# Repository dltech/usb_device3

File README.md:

# usb_device3
USB HID gamepad.
STM32 based USB adapter for ZX spectrum joystick. You may connect gamepad
with d-pad and two buttons to PC using USB.
Tested and working.

Project structure:\
/result - here is all usefull files to try this project (firmware binary, schematic and pcb template)\
/lib - basic code directory\
/lib/regs - stm32 MCU registers (lowest micriocontroller API level)\
/lib/STM32F103_CMSIS/ - MCU specific part of CMSIS\
/lib/CMSIS_5 - ARM CMSIS abstraction level directly from arm, as a submodule\
fpjat - build and upload script (for xubuntu, needs gcc arm toolchain and st-link, see pdf)\
/doc - project documentation in tex\
/datasheet - all related documentation (datasheets, standards)\
/sch - KiCAD schematic project\
More information about device is in blog:\
https://dltecc.blogspot.com/2021/10/continue-on-your-own-risk-cmsis-v5.html \
https://dltecc.blogspot.com/2021/09/report-descriptor-example.html \
https://dltecc.blogspot.com/2021/11/usb-hid-driver-for-stm32.html

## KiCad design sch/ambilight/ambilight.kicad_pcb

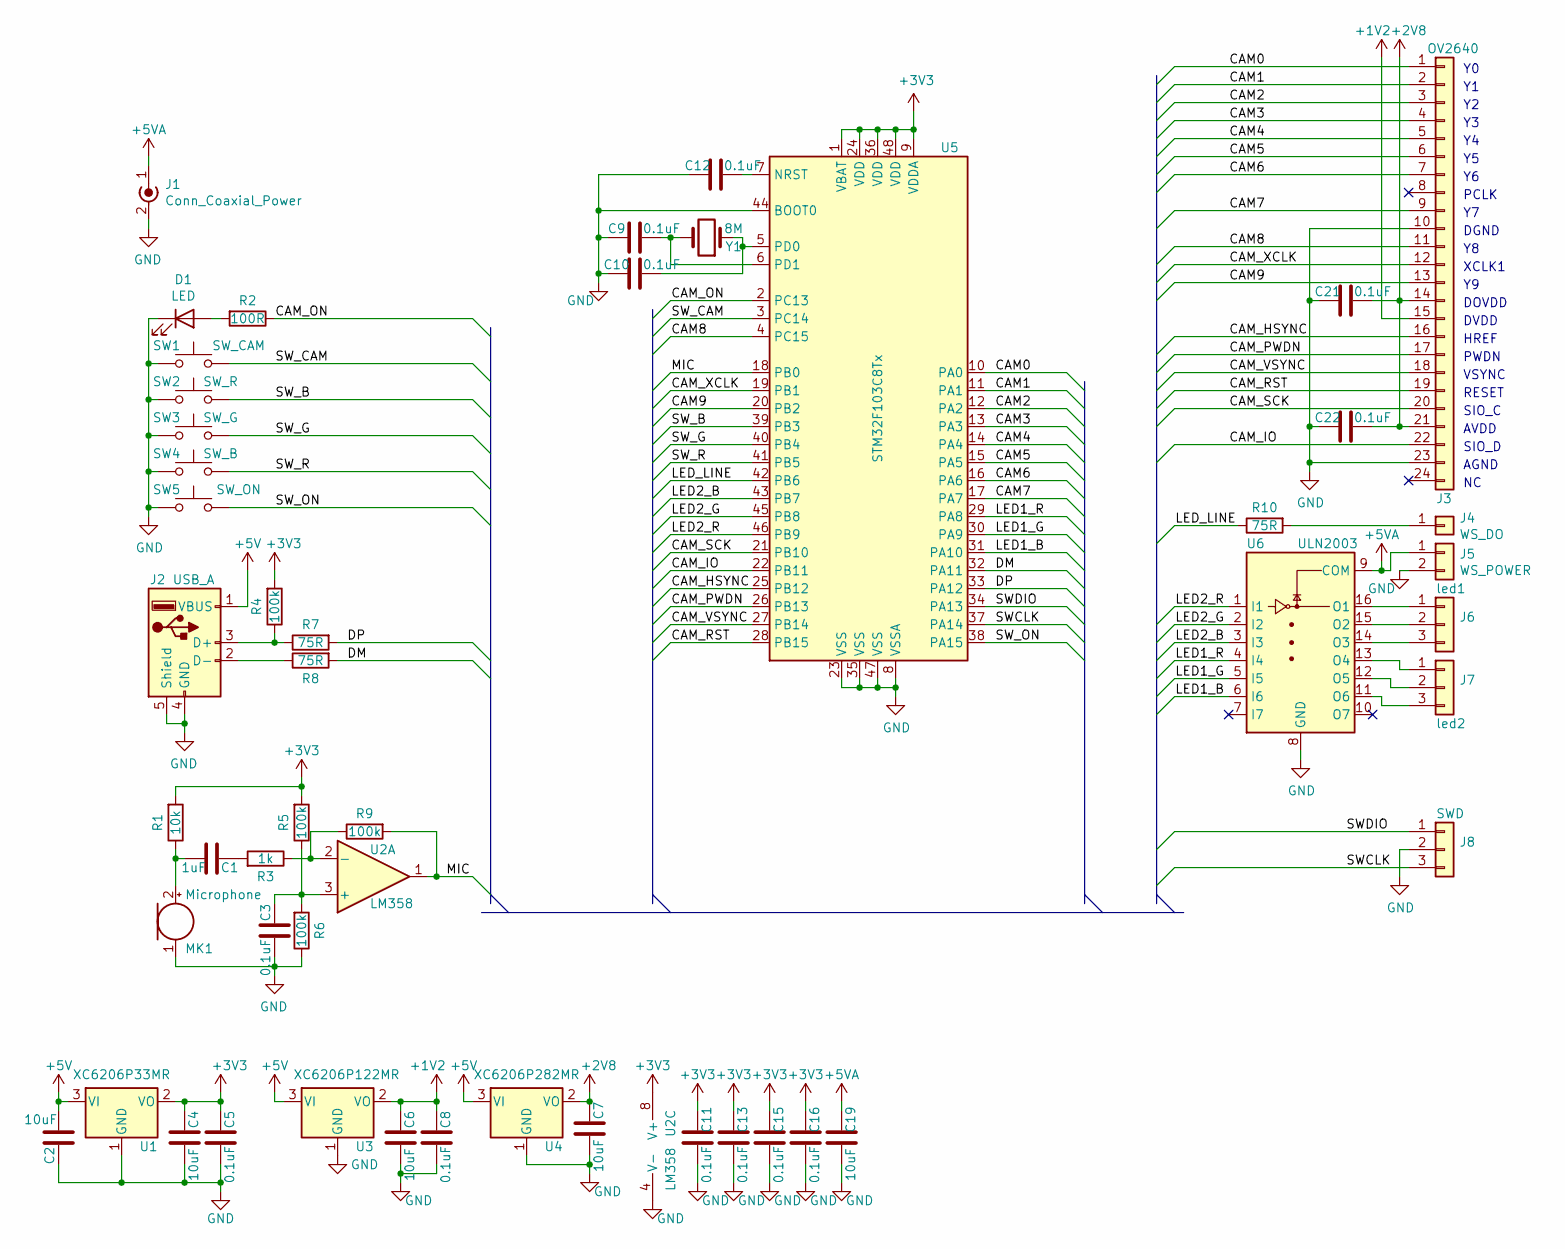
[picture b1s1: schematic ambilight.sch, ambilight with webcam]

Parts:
C1: 1uF; C_0805_2012Metric
C2, C4, C6, C7, C19: 10uF; C_0805_2012Metric
C3, C5, C8, C9, C10, C11, C12, C13, C15, C16, C21, C22: 0.1uF; C_0402_1005Metric
D1: LED; LED_0805_2012Metric
J1: Conn_Coaxial_Power; PinHeader_1x02_P2.54mm_Vertical
J2: USB_A; PinHeader_1x04_P2.54mm_Vertical
J3: OV2640; Hirose_FH12-24S-0.5SH_1x24-1MP_P0.50mm_Horizontal
J4: WS_DO; PinHeader_1x01_P2.54mm_Vertical
J5: WS_POWER; PinHeader_1x02_P2.54mm_Vertical
J6: led1; PinHeader_1x03_P2.54mm_Vertical
J7: led2; PinHeader_1x03_P2.54mm_Vertical
J8: SWD; 3WIRE_PADS
MK1: Microphone; CP_Radial_D5.0mm_P2.50mm
R1: 10k; R_0402_1005Metric
R2: 100R; R_0402_1005Metric
R3: 1k; R_0402_1005Metric
R4, R5, R6, R9: 100k; R_0402_1005Metric
R7, R8, R10: 75R; R_0402_1005Metric
SW1: SW_CAM; smd_sw_ali
SW2: SW_R; smd_sw_ali
SW3: SW_G; smd_sw_ali
SW4: SW_B; smd_sw_ali
SW5: SW_ON; smd_sw_ali
U1: XC6206P33MR; SOT-23
U2: LM358; SO-8_3.9x4.9mm_P1.27mm
U3: XC6206P122MR; SOT-23
U4: XC6206P282MR; SOT-23
U5: STM32F103C8Tx; LQFP-48_7x7mm_P0.5mm
U6: ULN2003; SOIC-16_3.9x9.9mm_P1.27mm
Y1: 8M; Crystal_SMD_5032-2Pin_5.0x3.2mm

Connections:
+1V2: C6.2, C8.2, J3.15, U3.2 (VO)
+2V8: C7.2, C21.1, C22.1, J3.14, J3.21, U4.2 (VO)
+3V3: C4.2, C5.2, C11.2, C13.2, C15.2, C16.2, R1.2, R4.2, R5.2, U1.2 (VO), U2.8 (V+), U5.1 (VBAT), U5.9 (VDDA), U5.24 (VDD), U5.36 (VDD), U5.48 (VDD)
+5V: C2.2, J2.1 (VBUS), U1.3 (VI), U3.3 (VI), U4.3 (VI)
+5VA: C19.2, J1.1 (In), J5.1, U6.9 (COM)
/CAM0: J3.1, U5.10 (PA0)
/CAM1: J3.2, U5.11 (PA1)
/CAM2: J3.3, U5.12 (PA2)
/CAM3: J3.4, U5.13 (PA3)
/CAM4: J3.5, U5.14 (PA4)
/CAM5: J3.6, U5.15 (PA5)
/CAM6: J3.7, U5.16 (PA6)
/CAM7: J3.9, U5.17 (PA7)
/CAM8: J3.11, U5.4 (PC15)
/CAM9: J3.13, U5.20 (PB2)
/CAM_HSYNC: J3.16, U5.25 (PB12)
/CAM_IO: J3.22, U5.22 (PB11)
/CAM_ON: R2.1, U5.2 (PC13)
/CAM_PWDN: J3.17, U5.26 (PB13)
/CAM_RST: J3.19, U5.28 (PB15)
/CAM_SCK: J3.20, U5.21 (PB10)
/CAM_VSYNC: J3.18, U5.27 (PB14)
/CAM_XCLK: J3.12, U5.19 (PB1)
/DM: R8.2, U5.32 (PA11)
/DP: R7.2, U5.33 (PA12)
/LED1_B: U5.31 (PA10), U6.6 (I6)
/LED1_G: U5.30 (PA9), U6.5 (I5)
/LED1_R: U5.29 (PA8), U6.4 (I4)
/LED2_B: U5.43 (PB7), U6.3 (I3)
/LED2_G: U5.45 (PB8), U6.2 (I2)
/LED2_R: U5.46 (PB9), U6.1 (I1)
/LED_LINE: R10.1, U5.42 (PB6)
/MIC: R9.2, U2.1, U5.18 (PB0)
/SWCLK: J8.3, U5.37 (PA14)
/SWDIO: J8.1, U5.34 (PA13)
/SW_B: SW2.2, U5.39 (PB3)
/SW_CAM: SW1.2, U5.3 (PC14)
/SW_G: SW3.2, U5.40 (PB4)
/SW_ON: SW5.2, U5.38 (PA15)
/SW_R: SW4.2, U5.41 (PB5)
GND: C2.1, C3.1, C4.1, C5.1, C6.1, C7.1, C8.1, C9.2, C10.2, C11.1, C12.2, C13.1, C15.1, C16.1, C19.1, C21.2, C22.2, D1.1 (K), J1.2 (Ext), J2.4 (GND), J2.5 (Shield), J3.10, J3.23, J5.2, J8.2, MK1.1 (-), R6.1, SW1.1, SW2.1, SW3.1, SW4.1, SW5.1, U1.1 (GND), U2.4 (V-), U3.1 (GND), U4.1 (GND), U5.8 (VSSA), U5.23 (VSS), U5.35 (VSS), U5.44 (BOOT0), U5.47 (VSS), U6.8 (GND)
unnamed: C1.1, R3.2
unnamed: C1.2, MK1.2 (+), R1.1
unnamed: C3.2, R5.1, R6.2, U2.3 (+)
unnamed: C9.1, U5.6 (PD1), Y1.2
unnamed: C10.1, U5.5 (PD0), Y1.1
unnamed: C12.1, U5.7 (NRST)
unnamed: D1.2 (A), R2.2
unnamed: J2.2 (D-), R8.1
unnamed: J2.3 (D+), R4.1, R7.1
unnamed: J4.1, R10.2
unnamed: J6.1, U6.16 (O1)
unnamed: J6.2, U6.15 (O2)
unnamed: J6.3, U6.14 (O3)
unnamed: J7.1, U6.13 (O4)
unnamed: J7.2, U6.12 (O5)
unnamed: J7.3, U6.11 (O6)
unnamed: R3.1, R9.1, U2.2 (-)

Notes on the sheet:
PCLK
DGND
XCLK1
DOVDD
DVDD
HREF
PWDN
VSYNC
RESET
SIO_C
AVDD
SIO_D
AGND

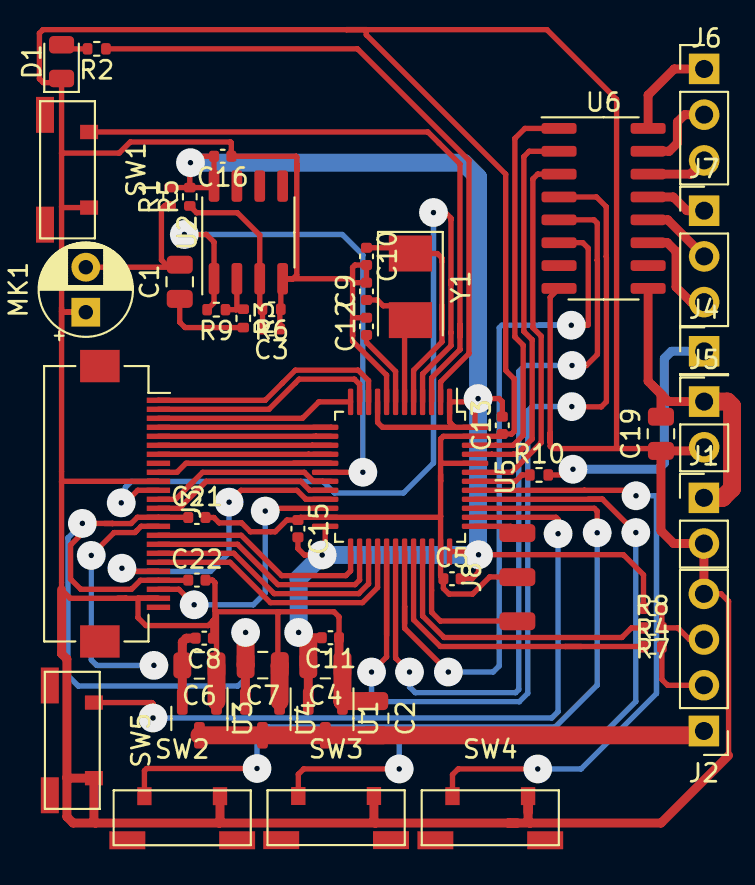
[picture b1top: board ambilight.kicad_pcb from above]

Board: 2 copper layers, 50 parts (0 on the bottom side), 58 nets.

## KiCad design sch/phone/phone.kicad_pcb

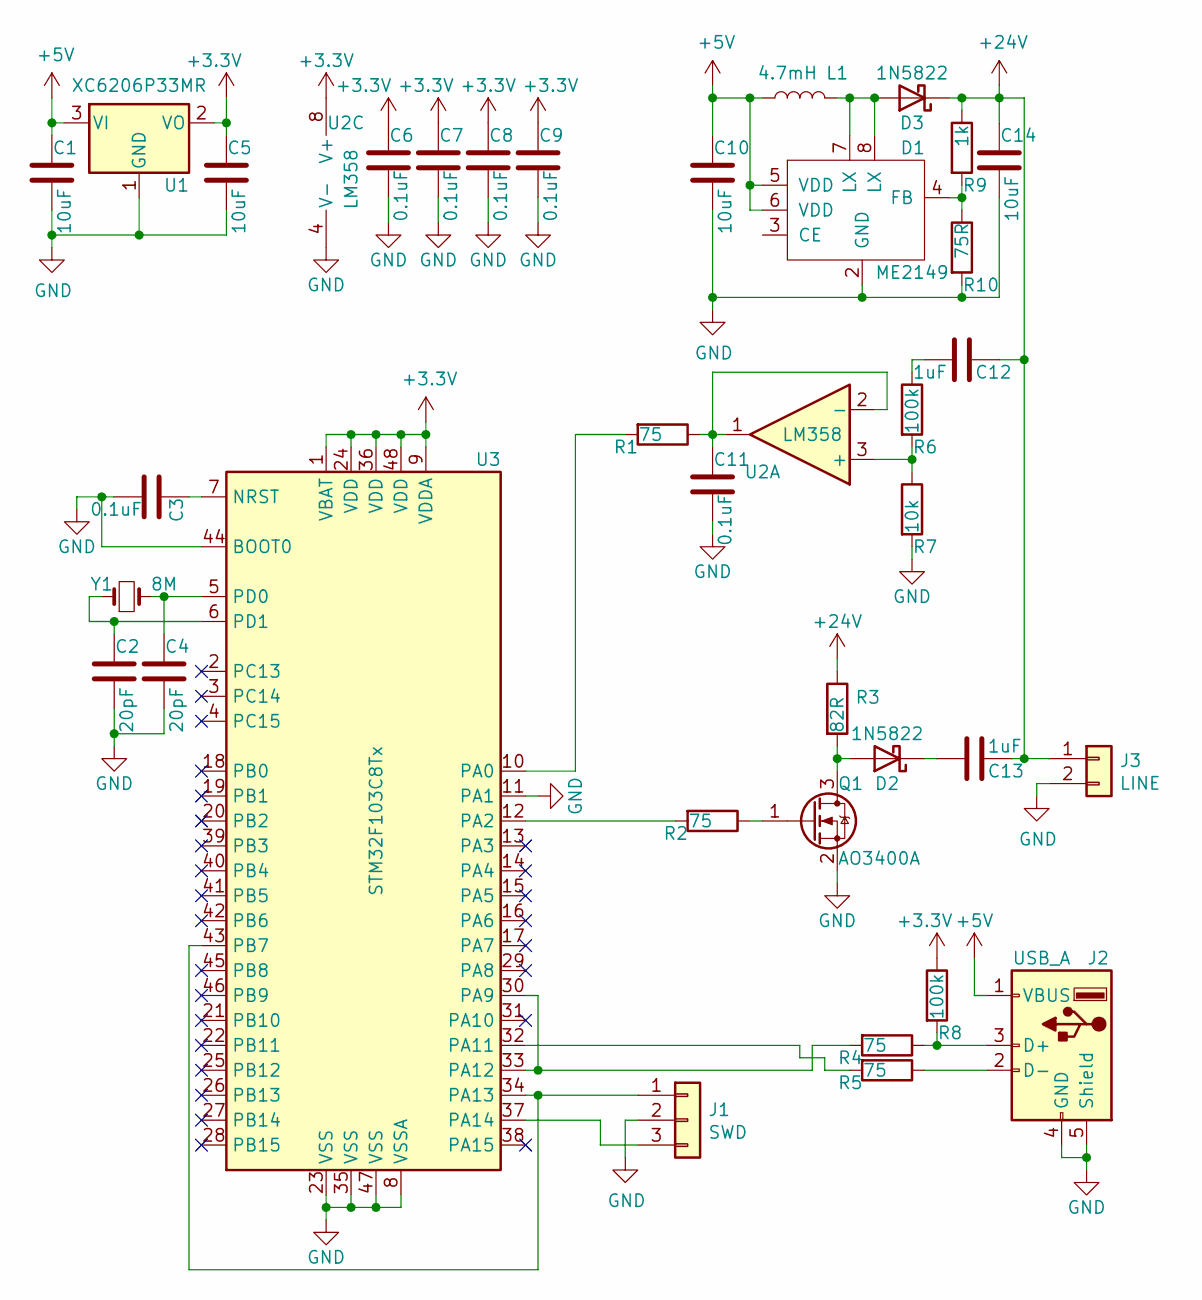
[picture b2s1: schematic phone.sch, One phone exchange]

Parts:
C1, C5, C10, C14: 10uF; C_0805_2012Metric
C2, C4: 20pF; C_0402_1005Metric
C3, C6, C7, C8, C9, C11: 0.1uF; C_0402_1005Metric
C12, C13: 1uF; C_0805_2012Metric
D1: ME2149; SO-8_3.9x4.9mm_P1.27mm
D2, D3: 1N5822; D_SMA
J1: SWD; 3WIRE_PADS
J2: USB_A; USB_A_CNCTech_1001-011-01101_Horizontal
J3: LINE; PinHeader_1x02_P1.27mm_Vertical
L1: 4.7mH; L_7.3x7.3_H3.5
Q1: AO3400A; SOT-23
R1, R2, R4, R5: 75; R_0402_1005Metric
R3: 82R; R_1206_3216Metric
R6, R8: 100k; R_0402_1005Metric
R7: 10k; R_0402_1005Metric
R9: 1k; R_0402_1005Metric
R10: 75R; R_0402_1005Metric
U1: XC6206P33MR; SOT-23
U2: LM358; SO-8_3.9x4.9mm_P1.27mm
U3: STM32F103C8Tx; LQFP-48_7x7mm_P0.5mm
Y1: 8M; Crystal_SMD_5032-2Pin_5.0x3.2mm

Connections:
+3V3: C5.1, C6.1, C7.1, C8.1, C9.1, R8.1, U1.2 (VO), U2.8 (V+), U3.1 (VBAT), U3.9 (VDDA), U3.24 (VDD), U3.36 (VDD), U3.48 (VDD)
+5V: C1.1, C10.1, D1.5 (VDD), D1.6 (VDD), J2.1 (VBUS), L1.1, U1.3 (VI)
+24V: C12.1, C13.1, C14.1, D3.1 (K), J3.1, R3.1, R9.1
GND: C1.2, C2.2, C3.2, C4.2, C5.2, C6.2, C7.2, C8.2, C9.2, C10.2, C11.2, C14.2, D1.2 (GND), J1.2, J2.4 (GND), J2.5 (Shield), J3.2, Q1.2 (S), R7.2, R10.2, U1.1 (GND), U2.4 (V-), U3.8 (VSSA), U3.11 (PA1), U3.23 (VSS), U3.35 (VSS), U3.44 (BOOT0), U3.47 (VSS)
unnamed: C2.1, U3.6 (PD1), Y1.1
unnamed: C3.1, U3.7 (NRST)
unnamed: C4.1, U3.5 (PD0), Y1.2
unnamed: C11.1, R1.1, U2.1, U2.2 (-)
unnamed: C12.2, R6.1
unnamed: C13.2, D2.1 (K)
unnamed: D1.4 (FB), R9.2, R10.1
unnamed: D1.7 (LX), D1.8 (LX), D3.2 (A), L1.2
unnamed: D2.2 (A), Q1.3 (D), R3.2
unnamed: J1.1, U3.34 (PA13), U3.43 (PB7)
unnamed: J1.3, U3.37 (PA14)
unnamed: J2.2 (D-), R5.1
unnamed: J2.3 (D+), R4.1, R8.2
unnamed: Q1.1 (G), R2.1
unnamed: R1.2, U3.10 (PA0)
unnamed: R2.2, U3.12 (PA2)
unnamed: R4.2, U3.30 (PA9), U3.33 (PA12)
unnamed: R5.2, U3.32 (PA11)
unnamed: R6.2, R7.1, U2.3 (+)

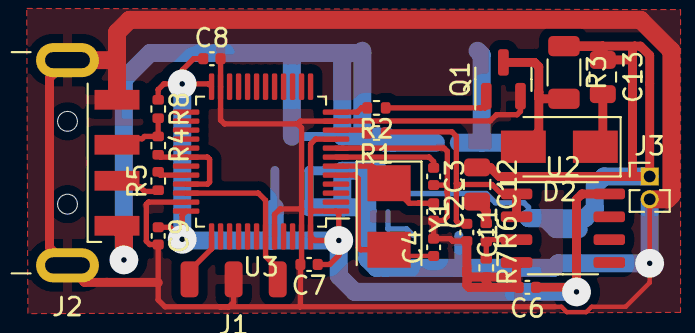
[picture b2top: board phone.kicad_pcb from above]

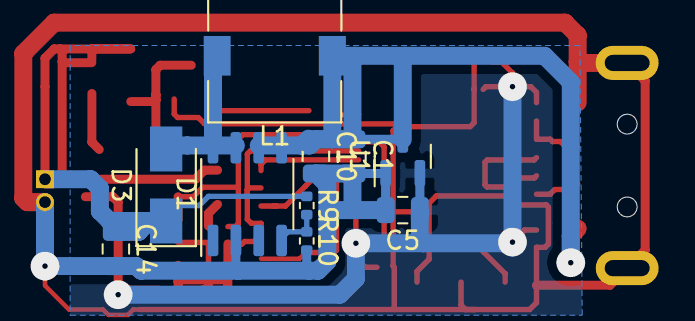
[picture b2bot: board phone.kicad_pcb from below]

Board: 2 copper layers, 36 parts (10 on the bottom side), 23 nets.

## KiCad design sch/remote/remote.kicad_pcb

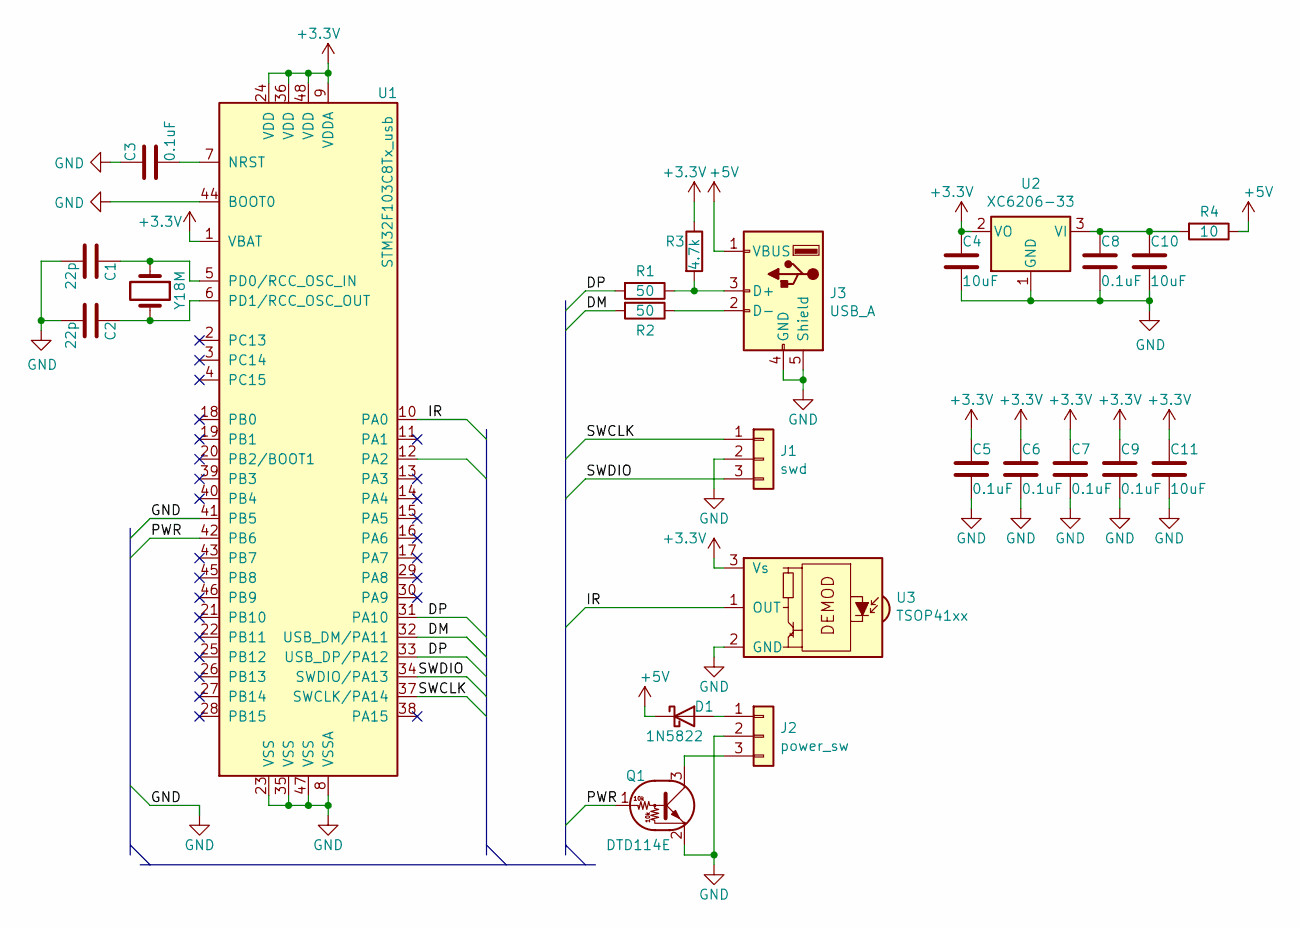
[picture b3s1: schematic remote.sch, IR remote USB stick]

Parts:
C1, C2: 22p; C_0402_1005Metric
C3, C5, C6, C7, C8, C9: 0.1uF; C_0402_1005Metric
C4, C10, C11: 10uF; C_0805_2012Metric
D1: 1N5822; D_SMA
J1: swd; 3WIRE_PADS
J2: power_sw; PinHeader_1x03_P2.54mm_Vertical
J3: USB_A; USB_A_CNCTech_1001-011-01101_Horizontal
Q1: DTD114E; SOT-23
R1, R2: 50; R_0402_1005Metric
R3: 4.7k; R_0402_1005Metric
R4: 10; R_0805_2012Metric
U1: STM32F103C8Tx_usb; LQFP-48_7x7mm_P0.5mm
U2: XC6206-33; SOT-23
U3: TSOP41xx; Vishay_MOLD-3Pin
Y1: 8M; Crystal_SMD_5032-2Pin_5.0x3.2mm

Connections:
+3V3: C4.1, C5.1, C6.1, C7.1, C9.1, C11.1, R3.1, U1.1 (VBAT), U1.9 (VDDA), U1.24 (VDD), U1.36 (VDD), U1.48 (VDD), U2.2 (VO), U3.3 (Vs)
+5V: D1.1 (K), J3.1 (VBUS), R4.1
/DM: R2.2, U1.32 (USB_DM/PA11)
/DP: R1.2, U1.31 (PA10), U1.33 (USB_DP/PA12)
/IR: U1.10 (PA0), U3.1 (OUT)
/PWR: Q1.1 (B), U1.42 (PB6)
/SWCLK: J1.1, U1.37 (SWCLK/PA14)
/SWDIO: J1.3, U1.34 (SWDIO/PA13)
GND: C1.2, C2.2, C3.1, C4.2, C5.2, C6.2, C7.2, C8.2, C9.2, C10.2, C11.2, J1.2, J2.2, J3.4 (GND), J3.5 (Shield), Q1.2 (E), U1.8 (VSSA), U1.23 (VSS), U1.35 (VSS), U1.41 (PB5), U1.44 (BOOT0), U1.47 (VSS), U2.1 (GND), U3.2 (GND)
unnamed: C1.1, U1.5 (PD0/RCC_OSC_IN), Y1.1
unnamed: C2.1, U1.6 (PD1/RCC_OSC_OUT), Y1.2
unnamed: C3.2, U1.7 (NRST)
unnamed: C8.1, C10.1, R4.2, U2.3 (VI)
unnamed: D1.2 (A), J2.1
unnamed: J2.3, Q1.3 (C)
unnamed: J3.2 (D-), R2.1
unnamed: J3.3 (D+), R1.1, R3.2

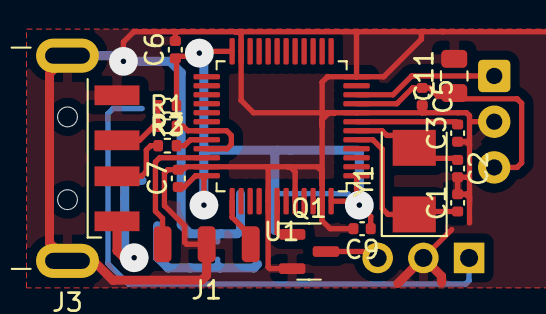
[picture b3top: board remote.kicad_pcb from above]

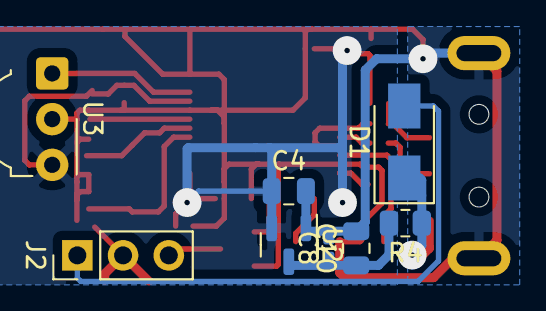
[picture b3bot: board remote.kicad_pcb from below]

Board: 2 copper layers, 24 parts (8 on the bottom side), 17 nets.

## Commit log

2021-06-01 lets begin!
2021-06-07 sch corrections
2021-06-11 usb core init
2021-06-13 hid desc
2021-06-14 desc
2021-06-22 usb device reg definitions
2021-06-29 request start to
2021-06-30 standard requests
2021-07-02 started HID descr
2021-07-03 buttons
2021-07-04 report update (not tested)
2021-07-06 req complete (not tested)
2021-07-12 some core functions
2021-07-13 reset
2021-07-16 susp/wkup
2021-07-19 almost
2021-07-21 Removed submodule
2021-07-21 compiled, go test
2021-07-21 alive but not workink
2021-07-21 no req, err
2021-07-23 catch SOF
2021-07-27 configure ok, lsusb detect, do not work (report desc?)
2021-07-28 comp detects
2021-07-31 err in pcb
2021-08-01 w debug info
2021-08-01 tested
2021-08-01 readme
2021-08-12 opt 5 lines
2021-08-12 forum
2021-08-17 begin to write normal documentation
2021-08-20 toolchain
2021-08-23 startup
2021-08-24 usb описание начал
2021-08-26 kicad libs
2021-08-26 video
2021-08-29 usb почти кратко про стандарт
2021-08-29 descriptor utility
2021-08-30 usb кратко
2021-09-03 запросики
2021-09-16 startup file поковырял
2021-09-18 флаги компиляции
2021-09-30 pic add
2021-10-01 documentation and startup file
2021-10-02 заполнил satrtup.c, по инструкции остался make и отладка
2021-10-02 заполнил раздел про отладку
2021-10-06 timer, gpio and rcc registers definitions
2021-10-06 almost compiled w new make and cmsis
2021-10-07 compiled
2021-10-07 compiled, not working
2021-10-10 without libopencm3, working
2021-10-10 cleaned
2021-10-11 pdf complete
2021-10-11 готоуо
2021-10-14 ld added
2021-11-13 binary
2022-01-11 started writing two more examples
2022-01-11 name of devices
2022-01-21 ir pdf downloaded
2022-01-22 schematic of ir dongle
2022-01-25 dma read of IR port
2022-01-26 descriptors, ciclycal read of IR, not tested
2022-01-26 sees in linux like keyboard
2022-01-29 keyboard driver test passed
2022-01-30 fixed gamepad
2022-03-03 0402 caps
2022-03-06 loger desc, new pcb for remote
2022-03-25 two layer IR, USB CDC almost compl
2022-03-27 port poll in loger
2022-03-30 cdc_req
2022-04-03 USART registers
2022-04-05 uart through DMA
2022-04-07 get descr req
2022-04-09 cdc driver ver.1
2022-04-09 vcp compiled, not tested
2022-04-09 PC sees VCP
2022-04-11 fix multipackage tx
2022-04-11 connects as ttyACM0, do not work
2022-04-11 strange loop vcp example
2022-04-11 setlinecoding fixed
2022-04-12 tested USB-UART
2022-04-12 some corrections
2022-04-19 убрался в файлах
2022-04-19 ir remote firmware OK, not tested
2022-04-19 working IR keyboard, tested
2022-04-22 add schematioc of ambilight
2022-04-22 add schematic of ambilight
2022-04-22 add schematic of phone exchange
2022-04-22 ambilight pcb
2022-04-23 ambilight buttons
2022-04-28 pdf's
